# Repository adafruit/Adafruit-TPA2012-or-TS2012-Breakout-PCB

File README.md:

## Adafruit TPA2012 or TS2012 Breakout PCB
<a href="http://www.adafruit.com/products/1552"><br/>
Click here to purchase one from the Adafruit shop</a>

This incredibly small stereo amplifier is surprisingly powerful - able to deliver 2 x 2.1W channels into 4 ohm impedance speakers (@ 10% THD). Inside the miniature chip is a class D controller, able to run from 2.7V-5.5VDC. Since the amp is a class D, it's incredibly efficient (89% efficient when driving an 8Ω speaker at 1.5 Watt) - making it perfect for portable and battery-powered projects. It has built in thermal and over-current protection but we could barely tell it got hot. This board is a welcome upgrade to basic "LM386" amps!

The inputs of the amplifier go through 1.0uF capacitors, so they are fully 'differential' - if you don't have differential outputs, simply tie the R- and L- to ground. The outputs are "Bridge Tied" - that means they connect directly to the outputs, no connection to ground. The output is a ~300KHz square wave PWM that is then 'averaged out' by the speaker coil - the high frequencies are not heard. All the above means that you can't connect the output into another amplifier, it should drive the speakers directly.

Comes with a fully assembled and tested breakout board with 1.0uF input capacitors. We also include a dual mini DIP switch for setting the amplifier gain on the fly, 3.5mm screw-terminal blocks so you can easily attach/detach your speakers, and some header in case you want to plug it into a breadboard. You will be ready to rock in 15 minutes!

PCB files for the Adafruit TPA2012 or TS2012 Stereo Class-D Audio Amp Breakout. The format is EagleCAD schematic and board layout
- https://www.adafruit.com/product/1552

### License

Adafruit invests time and resources providing this open source design, please support Adafruit and open-source hardware by purchasing products from [Adafruit](https://www.adafruit.com)!

All text above must be included in any redistribution

Designed by Limor Fried/Ladyada for Adafruit Industries.
Creative Commons Attribution/Share-Alike, all text above must be included in any redistribution. 
See license.txt for additional information.

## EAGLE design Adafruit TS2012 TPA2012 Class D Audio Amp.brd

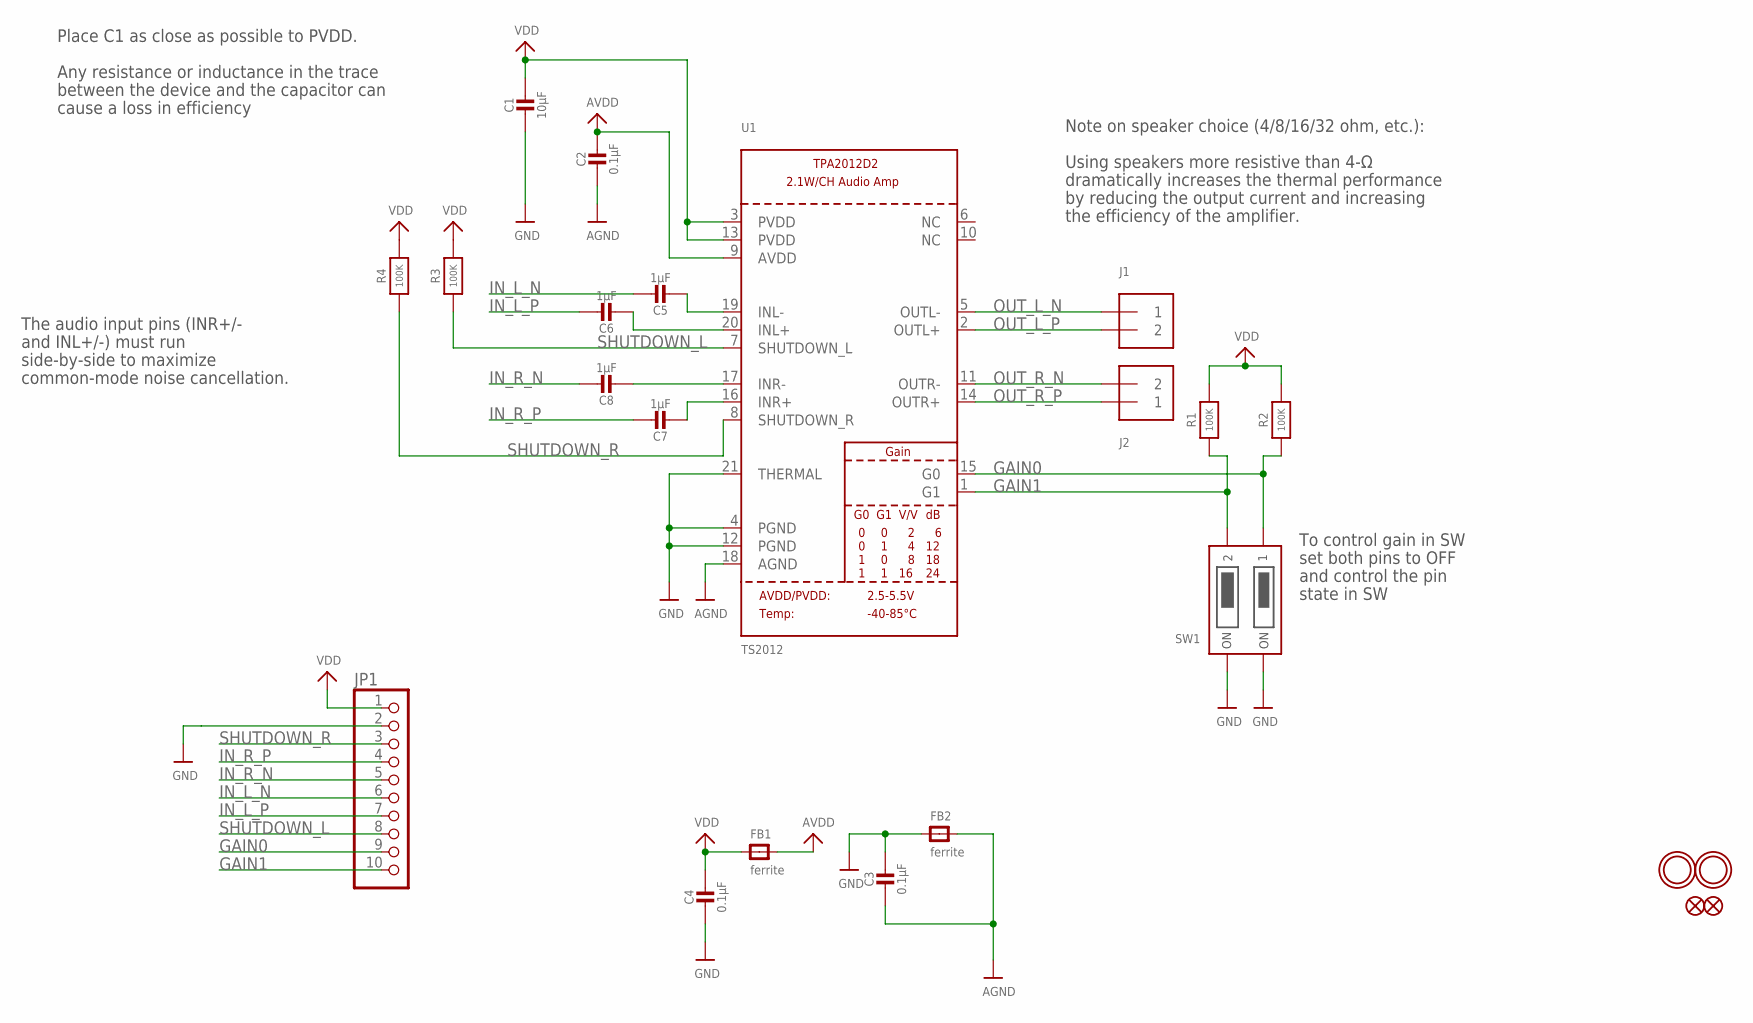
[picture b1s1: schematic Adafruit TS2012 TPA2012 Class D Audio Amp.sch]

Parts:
C1: 10µF; _0805MP
C2, C3, C4: 0.1µF; _0805MP
C5, C6, C7, C8: 1µF; _0805MP
FB1, FB2: ferrite; _0805MP
FID1, FID2: FIDUCIAL""; FIDUCIAL_1MM
J1, J2: TERMBLOCK_1X2; TERMBLOCK_1X2-3.5MM
JP1: HEADER-1X1070MIL; 1X10_ROUND70
R1, R2, R3, R4: 100K; _0805MP
SW1: DIPSWITCH_2PIN
U1: TS2012; WQFN20
U$20, U$21: MOUNTINGHOLE2.5_THICK; MOUNTINGHOLE_2.5_PLATED_THICK

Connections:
AGND: C2.2, C3.2, FB2.2, U1.18 (AGND)
AVDD: C2.1, FB1.2, U1.9 (AVDD)
GAIN0: JP1.9, R2.1, SW1.1OFF, U1.15 (G0)
GAIN1: JP1.10, R1.1, SW1.2OFF, U1.1 (G1)
GND: C1.2, C3.1, C4.2, FB2.1, JP1.2, SW1.1ON, SW1.2ON, U1.4 (PGND), U1.12 (PGND), U1.21 (THERMAL)
IN_L_N: C5.1, JP1.6
IN_L_P: C6.1, JP1.7
IN_R_N: C8.1, JP1.5
IN_R_P: C7.1, JP1.4
unnamed: C6.2, U1.20 (INL+)
unnamed: C5.2, U1.19 (INL-)
unnamed: C8.2, U1.17 (INR-)
unnamed: C7.2, U1.16 (INR+)
OUT_L_N: J1.1, U1.5 (OUTL-)
OUT_L_P: J1.2, U1.2 (OUTL+)
OUT_R_N: J2.2, U1.11 (OUTR-)
OUT_R_P: J2.1, U1.14 (OUTR+)
SHUTDOWN_L: JP1.8, R3.1, U1.7 (SHUTDOWN_L)
SHUTDOWN_R: JP1.3, R4.1, U1.8 (SHUTDOWN_R)
VDD: C1.1, C4.1, FB1.1, JP1.1, R1.2, R2.2, R3.2, R4.2, U1.3 (PVDD), U1.13 (PVDD)

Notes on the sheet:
To control gain in SW
set both pins to OFF
and control the pin
state in SW
Place C1 as close as possible to PVDD.
Any resistance or inductance in the trace
between the device and the capacitor can
cause a loss in efficiency
Using speakers more resistive than 4-Ω
dramatically increases the thermal performance
by reducing the output current and increasing
the efficiency of the amplifier.
Note on speaker choice (4/8/16/32 ohm, etc.):
The audio input pins (INR+/-
and INL+/-) must run
side-by-side to maximize
common-mode noise cancellation.

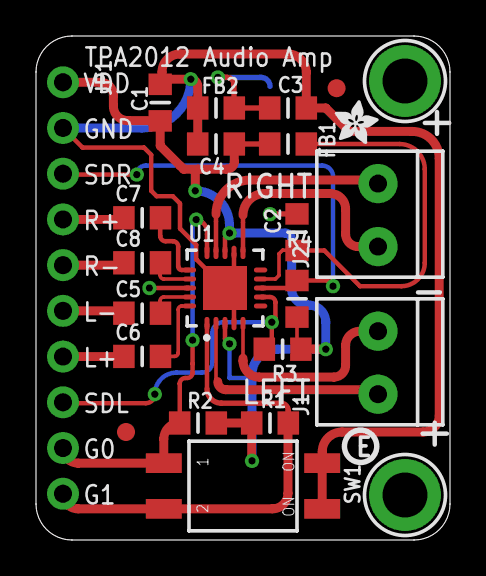
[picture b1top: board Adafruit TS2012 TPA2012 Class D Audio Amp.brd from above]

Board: 2 copper layers, 23.0 x 28.0 mm, 25 parts (0 on the bottom side), 20 nets.

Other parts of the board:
U$22: ADAFRUIT_2.5MM
U$23: PCBFEAT-REV-040

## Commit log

2016-06-21 init
